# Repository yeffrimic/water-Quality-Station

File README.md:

# water-Quality-Station
This is a repo with all the documentation to create, replicate and improve the quality water station from sincyt project

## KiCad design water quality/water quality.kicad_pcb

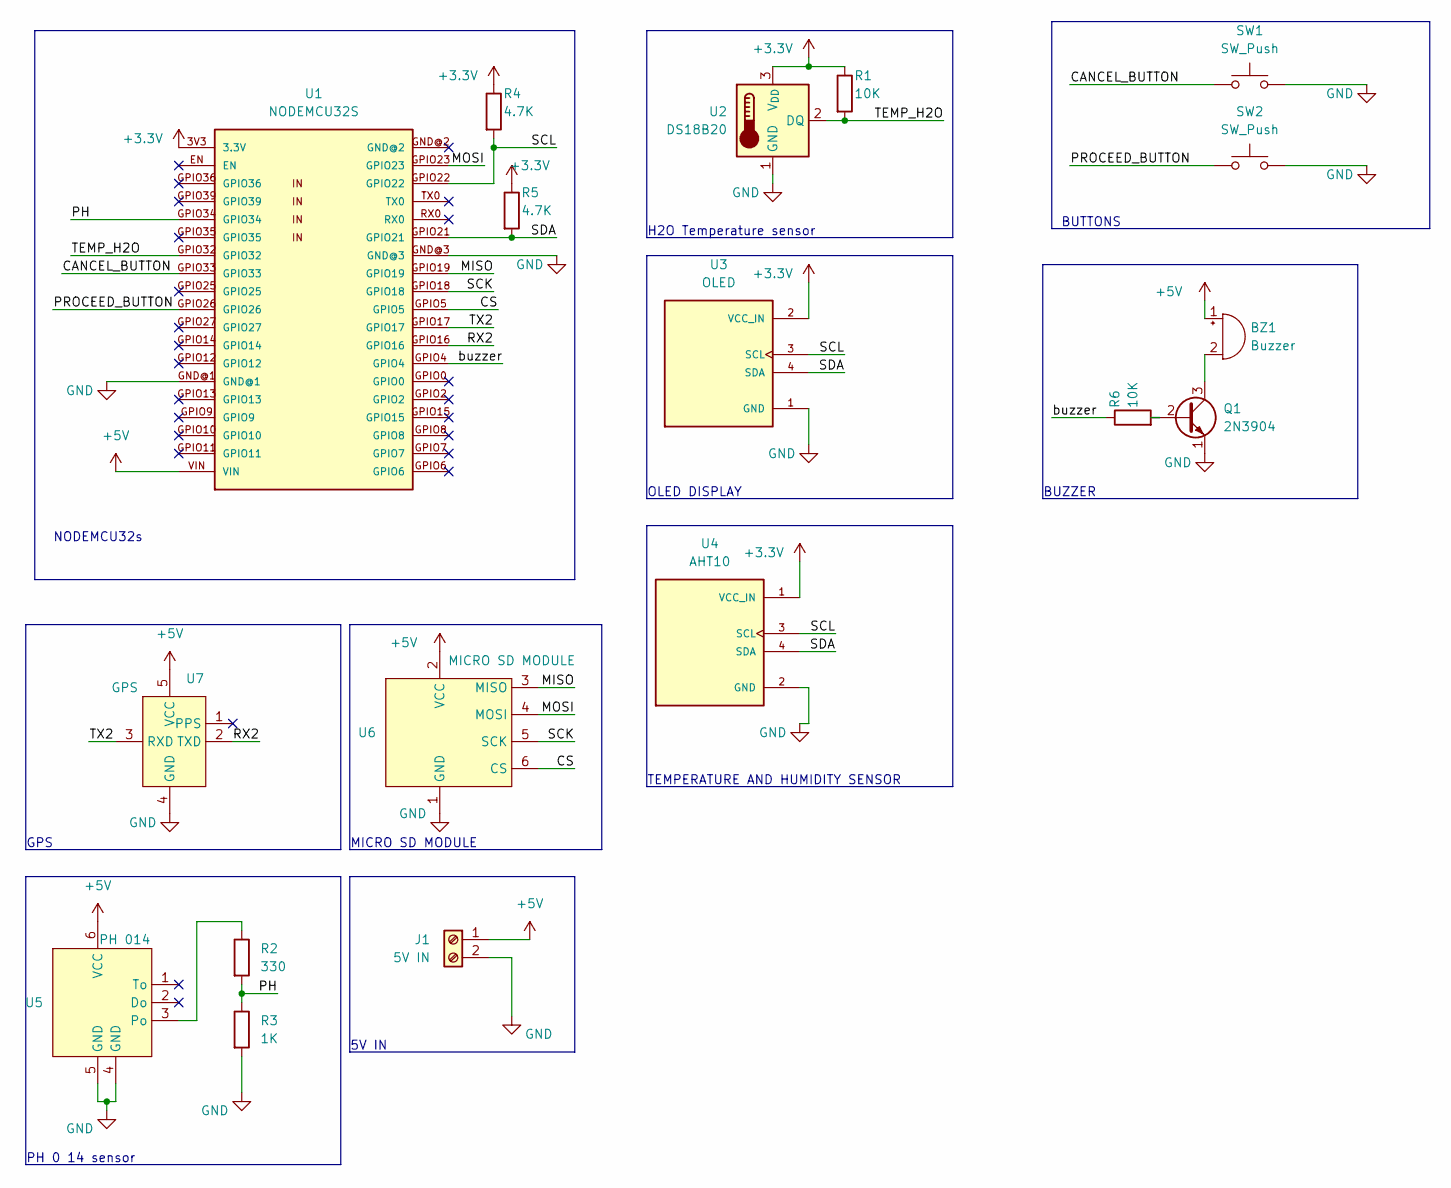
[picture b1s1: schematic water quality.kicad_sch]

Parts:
BZ1: Buzzer; Buzzer_12x9.5RM7.6
J1: 5V IN
Q1: 2N3904; TO-92_Inline
R1, R6: 10K; R_Axial_DIN0207_L6.3mm_D2.5mm_P10.16mm_Horizontal
R2: 330; R_Axial_DIN0207_L6.3mm_D2.5mm_P10.16mm_Horizontal
R3: 1K; R_Axial_DIN0207_L6.3mm_D2.5mm_P10.16mm_Horizontal
R4, R5: 4.7K; R_Axial_DIN0207_L6.3mm_D2.5mm_P10.16mm_Horizontal
SW1, SW2: SW_Push; SW_PUSH_6mm
U1: NODEMCU32S
U2: DS18B20; TerminalBlock_bornier-3_P5.08mm
U3: OLED; MODULE_DM-OLED096-636; PARTREV 2018-09-10
U4: AHT10; aht10; PARTREV 2018-09-10
U5: PH 014; ph sensor
U6: MICRO SD MODULE
U7: GPS; GPS neo6vm

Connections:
+3.3V: R1.1, R4.1, R5.1, U1.3V3 (3.3V), U2.3 (V_{DD}), U3.2 (VCC_IN), U4.1 (VCC_IN)
+5V: BZ1.1 (+), J1.1, U1.VIN, U5.6 (VCC), U6.2 (VCC), U7.5 (VCC)
/CANCEL_BUTTON: SW1.1, U1.GPIO33
/CS: U1.GPIO5, U6.6 (CS)
/MISO: U1.GPIO19, U6.3 (MISO)
/MOSI: U1.GPIO23, U6.4 (MOSI)
/PH: R2.2, R3.1, U1.GPIO34
/PROCEED_BUTTON: SW2.1, U1.GPIO26
/RX2: U1.GPIO16, U7.2 (TXD)
/SCK: U1.GPIO18, U6.5 (SCK)
/SCL: R4.2, U1.GPIO22, U3.3 (SCL), U4.3 (SCL)
/SDA: R5.2, U1.GPIO21, U3.4 (SDA), U4.4 (SDA)
/TEMP_H2O: R1.2, U1.GPIO32, U2.2 (DQ)
/TX2: U1.GPIO17, U7.3 (RXD)
/buzzer: R6.1, U1.GPIO4
GND: J1.2, Q1.1 (E), R3.2, SW1.2, SW2.2, U1.GND@1, U1.GND@3, U2.1 (GND), U3.1 (GND), U4.2 (GND), U5.4 (GND), U5.5 (GND), U6.1 (GND), U7.4 (GND)
unnamed: BZ1.2 (-), Q1.3 (C)
unnamed: Q1.2 (B), R6.2
unnamed: R2.1, U5.3 (Po)

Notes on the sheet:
5V IN
BUZZER
PH 0 14 sensor
OLED DISPLAY
H2O Temperature sensor
NODEMCU32s
MICRO SD MODULE
BUTTONS
TEMPERATURE AND HUMIDITY SENSOR
GPS

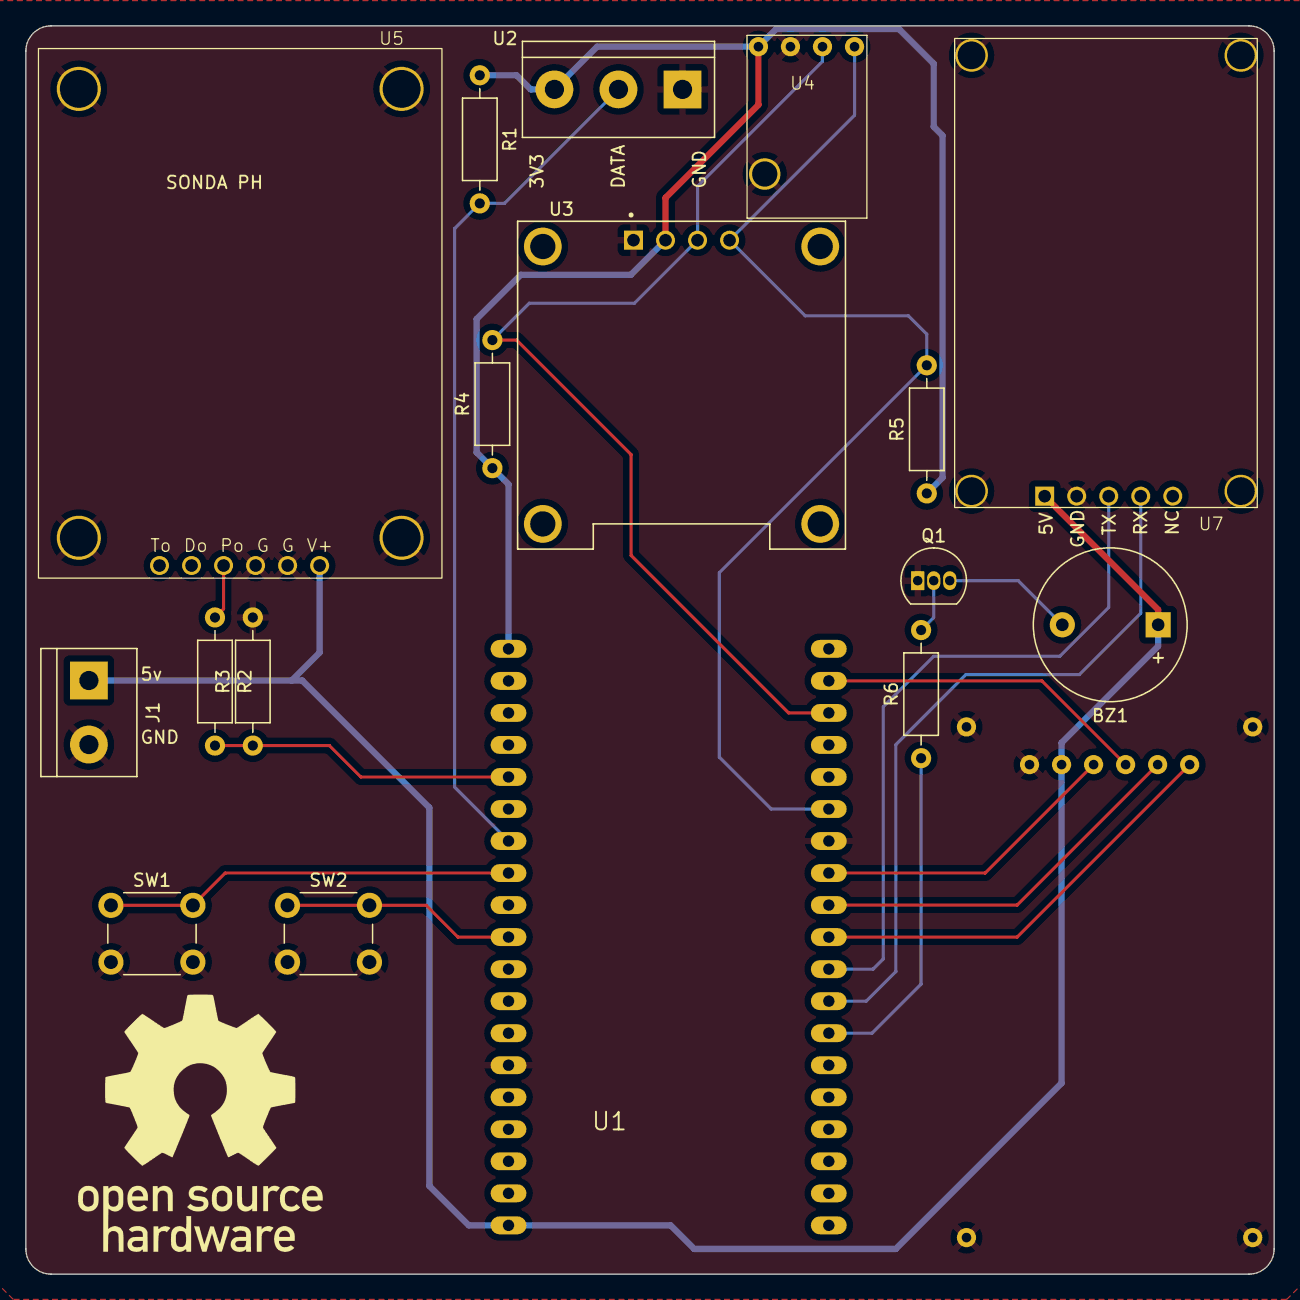
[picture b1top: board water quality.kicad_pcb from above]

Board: 4 copper layers, 99.0 x 99.0 mm, 18 parts (1 on the bottom side), 19 nets.

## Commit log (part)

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2024-04-30 code
2024-04-30 Rename rework_ducuchu.ino to code/code.ino
2024-04-30 add kicad files
